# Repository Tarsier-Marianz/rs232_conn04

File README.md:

# rs232_conn04

A prototype board for RS232 to USB connection.

### Thanks

[KiCad IDE](http://kicad-pcb.org/) - for letting me use a free software in designing PCB

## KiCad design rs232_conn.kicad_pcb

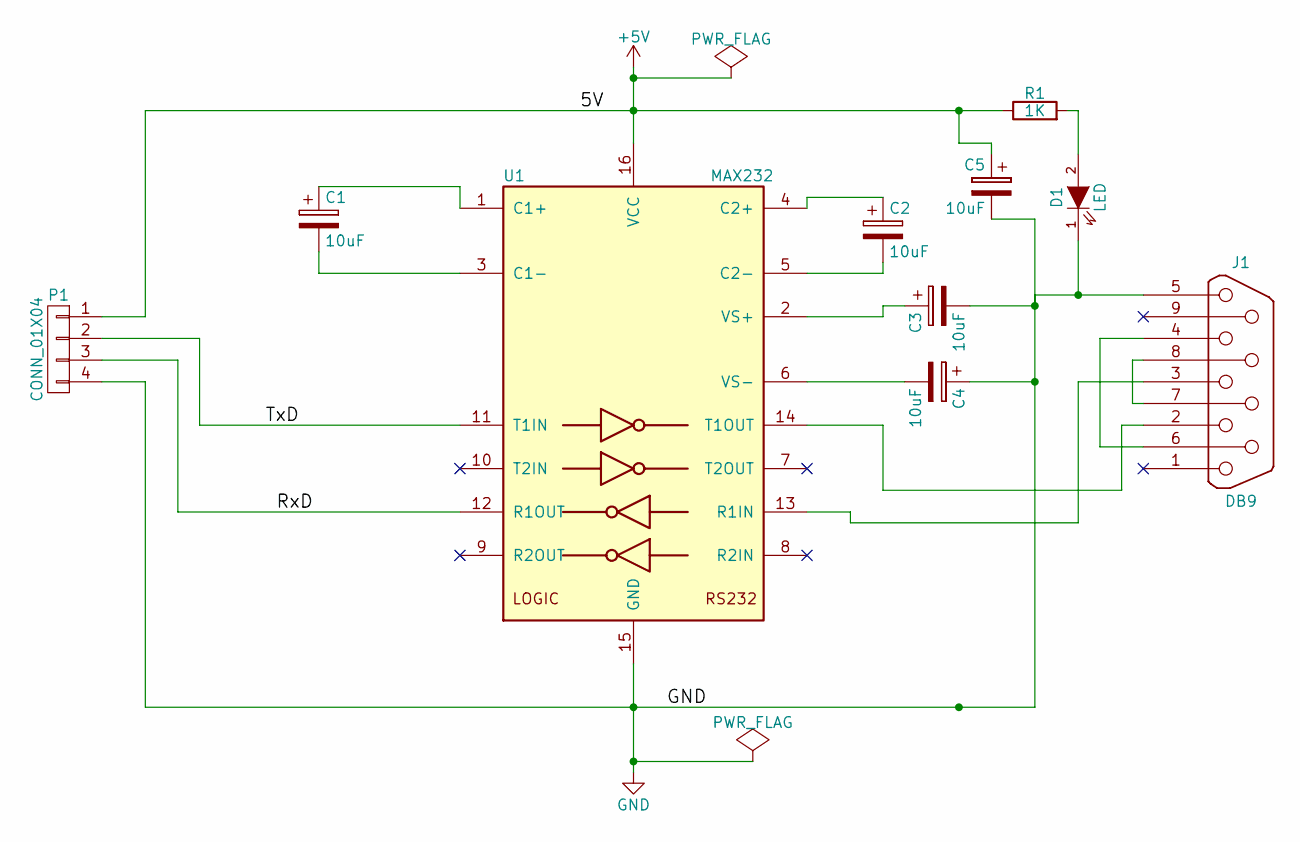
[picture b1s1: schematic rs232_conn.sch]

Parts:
C1, C2, C3, C4, C5: 10uF; C_1206_HandSoldering
D1: LED; LED_D3.0mm
J1: DB9; DB9F_CI
P1: CONN_01X04; Molex_KK-6410-04_04x2.54mm_Straight
R1: 1K; R_1206_HandSoldering
U1: MAX232; DIP-16_W7.62mm_LongPads

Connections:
+5V: C5.1, P1.1, R1.1, U1.16 (VCC)
/RxD: P1.3, U1.12 (R1OUT)
/TxD: P1.2, U1.11 (T1IN)
GND: C3.2, C4.1, C5.2, D1.1 (K), J1.5, P1.4, U1.15 (GND)
unnamed: C1.1, U1.1 (C1+)
unnamed: C1.2, U1.3 (C1-)
unnamed: C2.1, U1.4 (C2+)
unnamed: C2.2, U1.5 (C2-)
unnamed: C3.1, U1.2 (VS+)
unnamed: C4.2, U1.6 (VS-)
unnamed: D1.2 (A), R1.2
unnamed: J1.2, U1.14 (T1OUT)
unnamed: J1.3, U1.13 (R1IN)
unnamed: J1.4, J1.6
unnamed: J1.7, J1.8

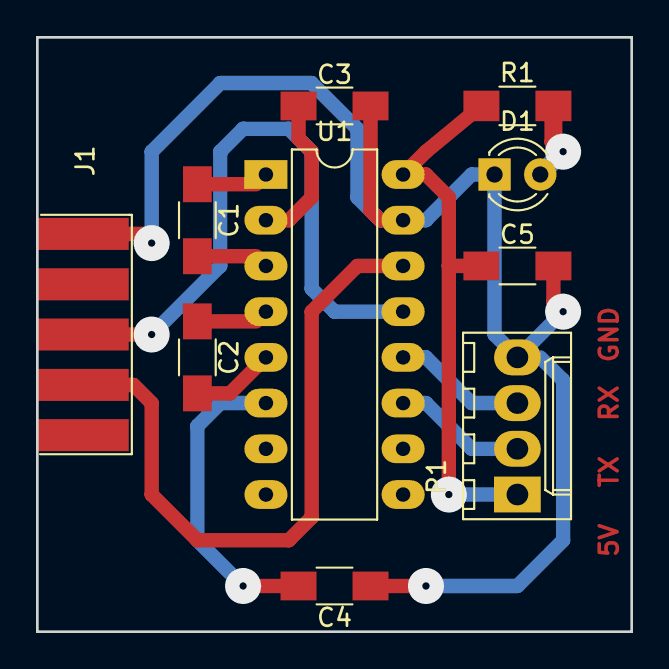
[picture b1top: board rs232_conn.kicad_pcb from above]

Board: 2 copper layers, 33.0 x 33.0 mm, 10 parts (0 on the bottom side), 15 nets.

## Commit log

2018-02-27 Add readme
